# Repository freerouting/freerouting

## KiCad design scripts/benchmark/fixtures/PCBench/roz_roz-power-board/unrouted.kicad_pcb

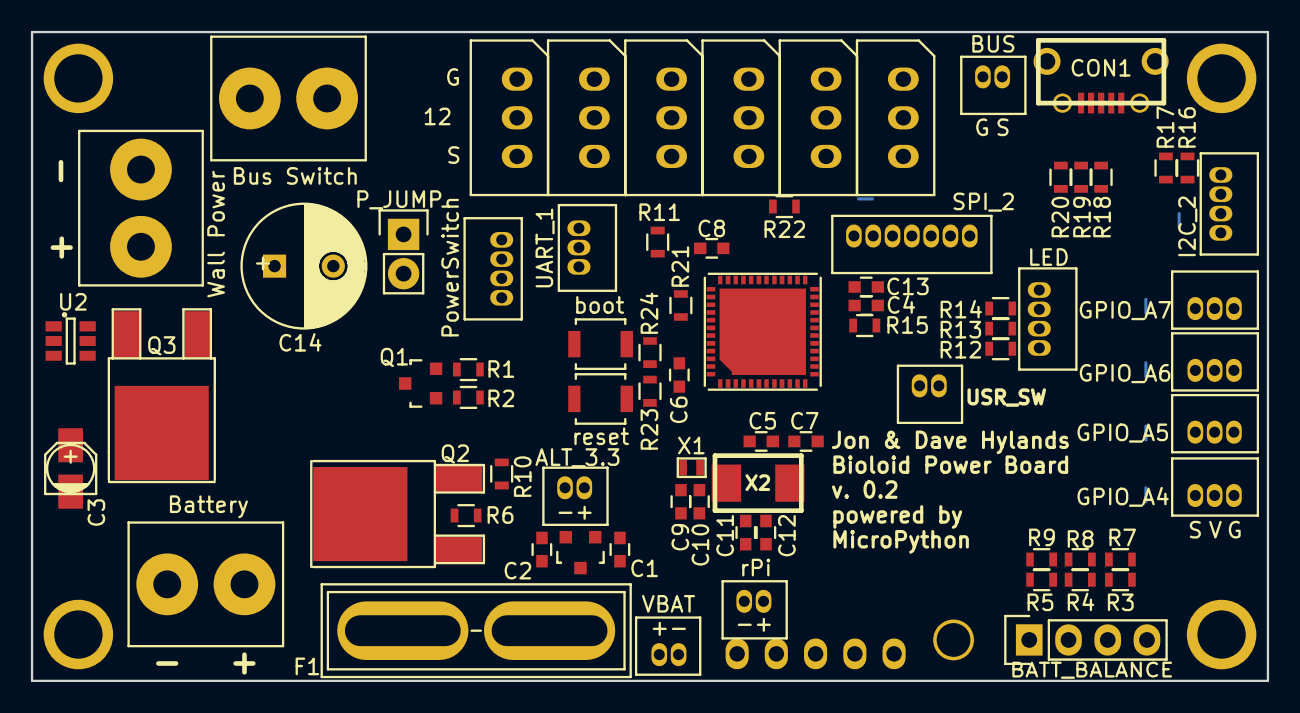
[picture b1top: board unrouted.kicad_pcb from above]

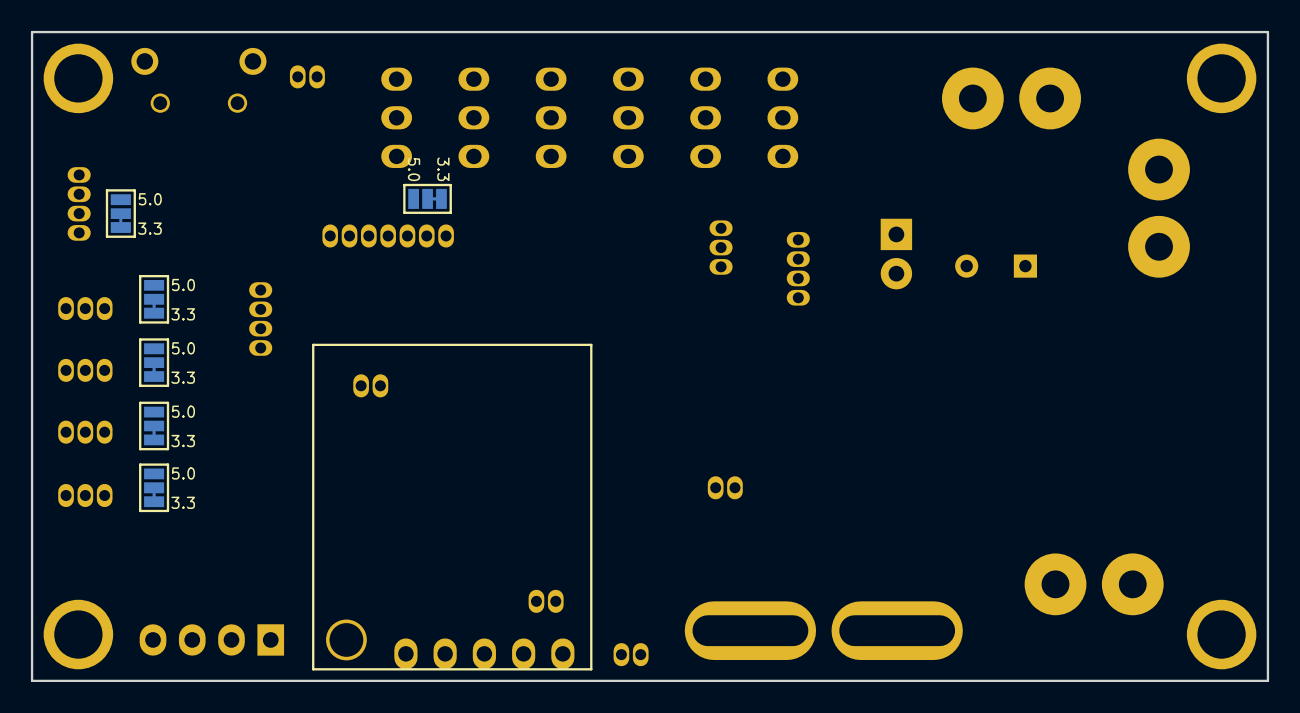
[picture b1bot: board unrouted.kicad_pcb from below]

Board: 2 copper layers, 80.0 x 42.0 mm, 87 parts (7 on the bottom side), 64 nets, no tracks yet.

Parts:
1PIN: P***; 2_56_hole
1PIN_2, 1PIN_3, 1PIN_4, 1PIN_5: P***; 4_40_hole
C1, C2, C4, C5, C6, C7, C8, C13: 0.1uF; C_0603
C3: 22uF; c_elec_3x5.3
C9, C10: 6pF; C_0603
C11, C12: 18pF; C_0603
C14: 680uF; C_Radial_D8_L21_P3.8
CON1: USB-MICRO-B; USB_MICRO_B
F1: FUSE; BladeFuse-CarType
J1, J2, J3, J4, J5, J6: Jumper_Switch; Jumper-Switch
P1: Wall Power; TerminalBlock
P2: Battery; TerminalBlock
P3: BATT_BALANCE; Socket_Strip_Straight_1x04
P4: ALT_3.3; SIL_2_050
P5: UART_1; SIL_3_050
P6: I2C_2; SIL_4_050
P7: SPI_2; SIL_7_050
P8: 5V Regulator; 5V_5A_VReg
P9: GPIO_A4; SIL_3_050
P10: GPIO_A5; SIL_3_050
P11: GPIO_A6; SIL_3_050
P12: GPIO_A7; SIL_3_050
P13: BIOLOID_BUS_1; Bioloid-3
P14: LED; SIL_4_050
P15: Bus Switch; TerminalBlock
P16: BIOLOID_BUS_2; Bioloid-3
P17: BIOLOID_BUS_3; Bioloid-3
P18: BIOLOID_BUS_4; Bioloid-3
P19: BIOLOID_BUS_5; Bioloid-3
P20: BIOLOID_BUS_6; Bioloid-3
P21: rPi; SIL_2_050
P23: USR_SW; SIL_2_050
P25: VBAT; SIL_2_050
P26: BUS; SIL_2_050
P_JUMP: P_JUMP; Socket_Strip_Straight_1x02
Q1: BS-170; SOT-23
Q2, Q3: STD30PF03LT4; TO-252-2Lead
R1, R10, R15, R21, R23: 10K; R_0603
R2: 100; R_0603
R3, R4, R5: 15K; R_0603
R6: 22K; R_0603
R7, R8, R9: 5K; R_0603
R11: 470K; R_0603
R12: 65; R_0603
R13: 0; R_0603
R14: 5; R_0603
R16, R17: 4.7K; R_0603
R18: 1K; R_0603
R19, R20: 20; R_0603
R22, R24: 100K; R_0603
SW2: PowerSwitch; SIL_4_050
SW3: RESET_SW; PUSH_SMT
SW4: BOOT_SW; PUSH_SMT
U1: AP7333; SOT-23
U2: LTC4412; SOT-23-6
U3: STM32F401xD_UFQFPN48; UFQFPN48
X1: 32.768kHz; CRYSTAL_SMT_3
X2: 8MHz; CRYSTAL_SMT

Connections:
+3V3: C2.1, C6.2, C7.2, C8.2, C13.2, J1.3, J2.3, J3.3, J4.3, J5.3, J6.3, P4.1, R11.2, R16.2, R17.2, R22.2, R23.1, SW2.3, SW4.2, U1.2, U3.9, U3.24, U3.36, U3.48
+5V: C1.1, J1.1, J2.1, J3.1, J4.1, J5.1, J6.1, P8.5, P21.1, U1.1
+12V: C14.1, P8.2, P15.2, Q2.2
+BATT: P2.2, Q3.2, U2.1
+F_POWER: F1.2, Q2.3, R6.2
+POWER: C3.1, F1.1, P1.2, Q3.3, U2.6
+SW_12V: P13.2, P15.1, P16.2, P17.2, P18.2, P19.2, P20.2
/OSC32_IN: C9.2, U3.3, X1.2
/OSC32_OUT: C10.2, U3.4, X1.1
/OSC_IN: C11.2, U3.5, X2.2
/OSC_OUT: C12.2, U3.6, X2.1
BIOLOID_TX: P13.1, P16.1, P17.1, P18.1, P19.1, P20.1, P26.1, U3.12
BOOT0: R24.2, SW4.1, U3.44, U3.45
CELL1_VOLTAGE: R5.1, R9.2, U3.10
CELL2_VOLTAGE: R4.1, R8.2, U3.11
CELL3_VOLTAGE: R3.1, R7.2, U3.13
GATE_PIN: R2.2, U3.37
GND: C1.2, C2.2, C3.2, C4.1, C5.1, C6.1, C7.1, C8.1, C9.1, C10.1, C11.1, C12.1, C13.1, C14.2, CON1.5, CON1.6, CON1.7, CON1.8, CON1.9, P1.1, P2.1, P3.1, P4.2, P5.3, P6.4, P7.7, P8.3, P8.4, P9.3, P10.3, P11.3, P12.3, P13.3, P14.1, P16.3, P17.3, P18.3, P19.3, P20.3, P21.2, P23.1, P25.2, P26.2, P_JUMP.1, Q1.2, R1.1, R7.1, R8.1, R9.1, R15.2, R21.2, R24.1, SW2.2, SW3.2, U1.3, U2.2, U2.3, U3.8, U3.23, U3.35, U3.47, U3.G1, U3.G2, U3.G3
GPIO_A4: P9.1, U3.14
GPIO_A5: P10.1, U3.15
GPIO_A6: P11.1, U3.16
GPIO_A7: P12.1, U3.17
I2C_2_SCL: P6.1, R17.1, U3.21
I2C_2_SDA: P6.2, R16.1, U3.39
LED_B: R14.1, R21.1, U3.41
LED_G: R13.1, U3.19
LED_R: R12.1, U3.18
unnamed: C4.2, U3.22
unnamed: C5.2, R23.2, SW3.1, U3.7
unnamed: CON1.1, R18.2
unnamed: CON1.2, R19.2
unnamed: CON1.3, R20.2
unnamed: J1.2, P6.3
unnamed: J2.2, P7.6
unnamed: J3.2, P9.2
unnamed: J4.2, P10.2
unnamed: J5.2, P11.2
unnamed: J6.2, P12.2
unnamed: P3.2, R5.2
unnamed: P3.3, R4.2
unnamed: P3.4, R3.2
unnamed: P14.2, R14.2
unnamed: P14.3, R13.2
unnamed: P14.4, R12.2
unnamed: P_JUMP.2, Q1.3, R10.1, SW2.1
unnamed: P23.2, U3.2
unnamed: Q1.1, R1.2, R2.1
unnamed: Q2.1, R6.1, R10.2
unnamed: Q3.1, U2.5
unnamed: R19.1, U3.32
unnamed: R20.1, U3.33
PA9: R18.1, U3.30
PA10: R22.1, U3.31
PB2: R15.1, U3.20
SPI_2_MISO: P7.2, U3.27
SPI_2_MOSI: P7.1, U3.28
SPI_2_SCK: P7.3, U3.26
SPI_CS_1: P7.4, U3.25
SPI_CS_2: P7.5, U3.29
STAT_PIN: R11.1, U2.4, U3.38
SWITCH_PIN: SW2.4, U3.34
UART_1_RX: P5.2, U3.43
UART_1_TX: P5.1, U3.42
VBAT: P25.1, U3.1

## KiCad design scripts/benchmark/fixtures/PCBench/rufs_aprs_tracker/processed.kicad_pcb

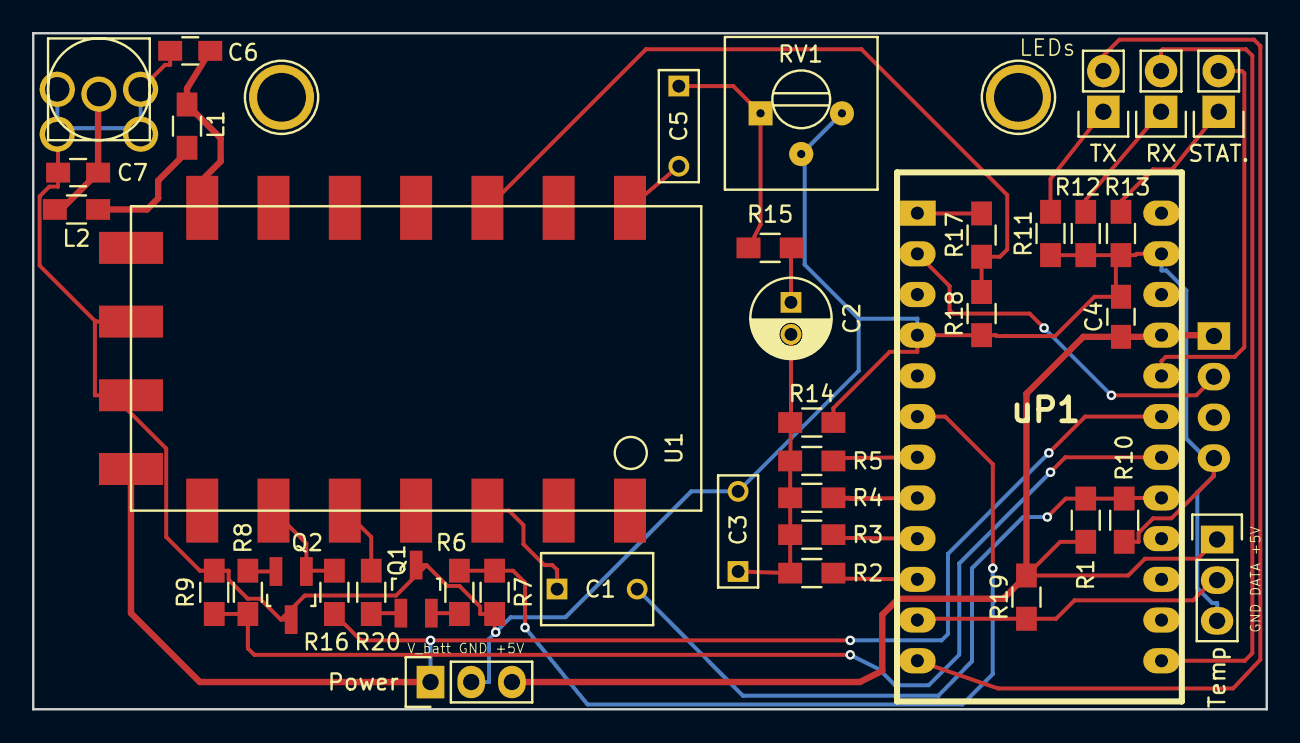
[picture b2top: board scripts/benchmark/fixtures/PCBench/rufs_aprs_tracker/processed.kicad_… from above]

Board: 2 copper layers, 77.0 x 42.2 mm, 41 parts (1 on the bottom side), 33 nets.

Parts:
C1: 1uF; C_Rect_L7_W4.5_P5
C2: 4.7uF; C_Radial_D5_L11_P2
C3, C5: 100nF; C_Rect_L7_W2.5_P5
C4: 100nF; C_0805_HandSoldering
C6, C7: 15pF; C_0805_HandSoldering
J1: SMA; sma_female_top
L1, L2: 0.027uH; R_0805_HandSoldering
P3: GPS; ublox_gps_breakout
Power: POWER; Pin_Header_Straight_1x03
Q1, Q2: 2N7002; SOT-23_Handsoldering
R1, R10, R15: 100K; R_0805_HandSoldering
R2: 1K 1%; R_0805_HandSoldering
R3: 2K2 1%; R_0805_HandSoldering
R4: 3K9 1%; R_0805_HandSoldering
R5: 8K2 1%; R_0805_HandSoldering
R6, R7, R8, R9: 1K; R_0805_HandSoldering
R11, R12, R13: 3K3; R_0805_HandSoldering
R14: 270 1%; R_0805_HandSoldering
R16, R17, R20: 10K; R_0805_HandSoldering
R18: 20K; R_0805_HandSoldering
R19: 4.7K; R_0805_HandSoldering
RV1: 10K; Potentiometer_Trimmer-Suntan-TSR-3386P
RX: RX (RED); Pin_Header_Straight_1x02
STAT.: STATUS (GREEN); Pin_Header_Straight_1x02
TX: TX (GREEN); Pin_Header_Straight_1x02
Temp: TEMPERATURE; Pin_Header_Straight_1x03
U1: DRA818V; dra818v
uP1: Pro Mini 5V 16MHz; ARDUINO_PRO_MINI

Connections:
+5V: C4.1, P3.1, Power.3, R1.2, R19.1, Temp.1, uP1.21
/AUDIO_IN: C1.2, R1.1, R10.1, uP1.17
/D4: R5.2, uP1.7
/D5: R4.2, uP1.8
/D6: R3.2, uP1.9
/D7: R2.2, uP1.10
/D9: TX.2, uP1.12
/D10: RX.2, uP1.13
/GPS_RX: P3.2, uP1.2
/LINE_LEVEL_IN: C1.1, U1.3
/MIC_LEVEL_OUT: C5.1, R15.1, RV1.1
/PTT_CONTROL: R6.2, R7.2, uP1.6
/PTT_V+: Q1.1, R20.2
/RADIO_PD: Q2.1, R16.2, U1.6
/RADIO_PD_CONTROL: R8.2, R9.2, uP1.18
/RADIO_TX: R17.1, R18.1, U1.16
/STATUS_LED: STAT..2, uP1.20
/TEMP_DATA: R19.2, Temp.2, uP1.11
/V_BATT: Power.1, R16.1, U1.8, uP1.19
GND: C3.2, C4.2, C6.2, C7.2, J1.2, J1.3, J1.4, J1.5, P3.4, Power.2, Q1.3, Q2.3, R7.1, R9.1, R10.2, R11.1, R12.1, R13.1, R14.2, R18.2, RV1.2, RV1.3, Temp.3, U1.9, U1.10, uP1.4, uP1.23
unnamed: C2.1, R15.2
unnamed: C2.2, C3.1, R2.1, R3.1, R4.1, R5.1, R14.1
unnamed: C5.2, U1.18
unnamed: C6.1, L1.1, U1.12
unnamed: C7.1, J1.1, L2.2
unnamed: R11.2, TX.1
unnamed: R12.2, RX.1
unnamed: R13.2, STAT..1
unnamed: L1.2, L2.1
unnamed: Q1.2, R6.1
unnamed: Q2.2, R8.1
unnamed: R17.2, uP1.1
unnamed: R20.1, U1.5

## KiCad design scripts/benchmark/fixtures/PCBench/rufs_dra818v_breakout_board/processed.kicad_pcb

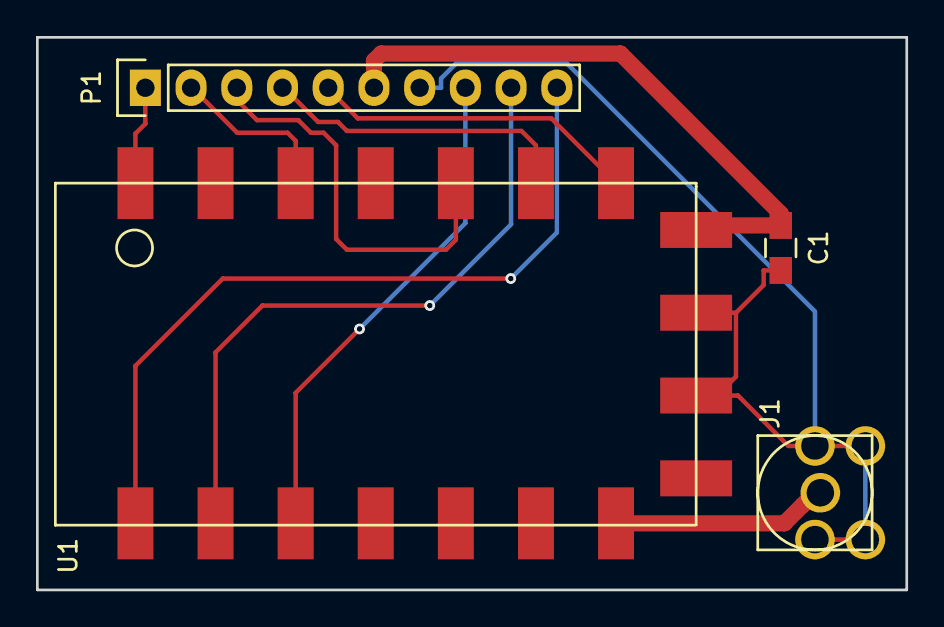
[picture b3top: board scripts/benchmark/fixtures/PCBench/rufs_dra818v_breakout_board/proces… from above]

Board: 2 copper layers, 48.3 x 30.7 mm, 4 parts (0 on the bottom side), 11 nets.

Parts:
C1: 100nF X7R; C_0805_HandSoldering
J1: SMA female; sma_female_top
P1: CONN_01X10; Pin_Header_Straight_1x10
U1: DRA818V; dra818v

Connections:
GND: C1.2, J1.2, J1.3, J1.4, J1.5, P1.7, U1.9, U1.10
unnamed: J1.1, U1.12
unnamed: P1.1, U1.1
unnamed: P1.2, U1.3
unnamed: P1.3, U1.5
unnamed: P1.4, U1.6
unnamed: P1.5, U1.7
unnamed: P1.8, U1.16
unnamed: P1.9, U1.17
unnamed: P1.10, U1.18
VCC: C1.1, P1.6, U1.8

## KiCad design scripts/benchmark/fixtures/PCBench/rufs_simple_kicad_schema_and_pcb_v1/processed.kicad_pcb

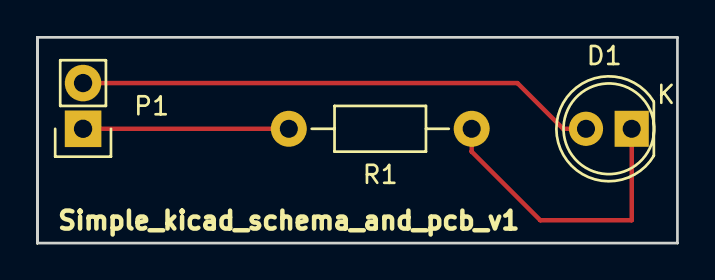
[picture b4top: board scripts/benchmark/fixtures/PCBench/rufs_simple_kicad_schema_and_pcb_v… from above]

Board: 2 copper layers, 35.6 x 11.4 mm, 3 parts (0 on the bottom side), 3 nets.

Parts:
D1: LED; LED-5MM
P1: Power; Pin_Header_Straight_1x02
R1: 330; Resistor_Horizontal_RM10mm

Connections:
GND: D1.2, P1.2
unnamed: D1.1, R1.1
VCC: P1.1, R1.2
